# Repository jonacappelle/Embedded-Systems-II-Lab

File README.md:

# LAB: Embedded Systems II

## SOFTWARE

- [IMU](https://github.com/jonacappelle/Embedded-Systems-II-Lab/tree/master/Jona%20-%20IMU%20and%20Main%20PCB/Embedded_II_ICM_20948)
- [Game](https://github.com/jonacappelle/Embedded-Systems-II-Lab/tree/master/Niels%20-%20Code%20spel/SLSTK3400A_blink)
- [LoRa](https://github.com/jonacappelle/Embedded-Systems-II-Lab/tree/master/Pieter%20-%20Connectivity%20and%20Visualisation)

## HARDWARE

[Main board](https://github.com/jonacappelle/Embedded-Systems-II-Lab/tree/master/Jona%20-%20IMU%20and%20Main%20PCB/EFM32_ICM20948_PCB)  
[Energy harvesting](https://github.com/jonacappelle/Embedded-Systems-II-Lab/tree/master/Daan%20-%20VoedingDesign%20PCB/schema_pcb)

### MAIN BOARD: µC + Compass + LoRa

### POWER BOARD

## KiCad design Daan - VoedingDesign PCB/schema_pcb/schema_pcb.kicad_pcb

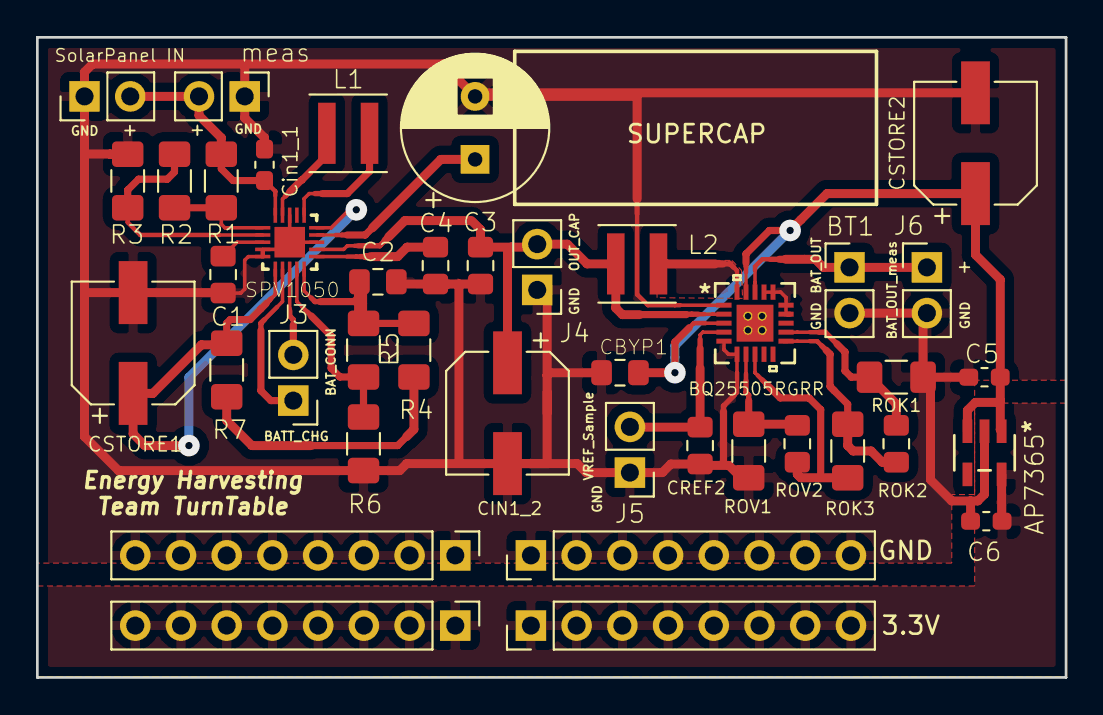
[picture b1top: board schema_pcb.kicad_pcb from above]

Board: 2 copper layers, 57.2 x 35.6 mm, 37 parts (0 on the bottom side), 24 nets.

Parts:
3.3V: Conn_3V3_2; PinHeader_1x08_P2.54mm_Vertical
BT1: Battery_Cell; PinHeader_1x02_P2.54mm_Vertical
C1: 10 nF; C_0805_2012Metric_Pad1.15x1.40mm_HandSolder
C2: 470 nF; C_0805_2012Metric_Pad1.15x1.40mm_HandSolder
C3, C4: 100 nF; C_0805_2012Metric_Pad1.15x1.40mm_HandSolder
C5, C6: 1u; C_0603_1608Metric_Pad1.05x0.95mm_HandSolder
CBYP1: 0.1 uF; C_0805_2012Metric_Pad1.15x1.40mm_HandSolder
CIN1_2: 4.7 uF; CP_Elec_6.3x5.3
CREF2: 100 nF; C_0805_2012Metric_Pad1.15x1.40mm_HandSolder
CSTORE1: 47 uF; CP_Elec_6.3x5.3
CSTORE2: 4.7 uF; CP_Elec_6.3x5.3
Cin1_1: 1 uF; C_0603_1608Metric_Pad1.05x0.95mm_HandSolder
GND: Conn_GND; PinHeader_1x08_P2.54mm_Vertical
J3: output_connect_pins; PinHeader_1x02_P2.54mm_Vertical
J4: conn_supercap_meas_volt; PinHeader_1x02_P2.54mm_Vertical
J5: conn_meas_VREF_Sample; PinHeader_1x02_P2.54mm_Vertical
J6: conn_meas_battery; PinHeader_1x02_P2.54mm_Vertical
L1, L2: 22 uH; L_Coilcraft_XxL4040
R1: 10 M; R_1206_3216Metric_Pad1.42x1.75mm_HandSolder
R2: 560 K; R_1206_3216Metric_Pad1.42x1.75mm_HandSolder
R3: 2.7 M; R_1206_3216Metric_Pad1.42x1.75mm_HandSolder
R4: 3.9 M; R_1206_3216Metric_Pad1.42x1.75mm_HandSolder
R5: 1.5 M; R_1206_3216Metric_Pad1.42x1.75mm_HandSolder
R6: 7.5 M; R_1206_3216Metric_Pad1.42x1.75mm_HandSolder
R7: 3.3 M; R_1206_3216Metric_Pad1.42x1.75mm_HandSolder
ROK1: 5.23; R_1206_3216Metric_Pad1.42x1.75mm_HandSolder
ROK2: 6.34 M; R_0805_2012Metric_Pad1.15x1.40mm_HandSolder
ROK3: 1.3 M; R_1206_3216Metric_Pad1.42x1.75mm_HandSolder
ROV1: 5.62 M; R_1206_3216Metric_Pad1.42x1.75mm_HandSolder
ROV2: 7.32 M; R_0805_2012Metric_Pad1.15x1.40mm_HandSolder
SPV1050: SPV1050TTR; QFN40P300X300X100-21N
SUPERCAP: 3.3 F; CP_Radial_D8.0mm_P3.50mm
SolarPanel IN: conn_solarpanel; PinHeader_1x02_P2.54mm_Vertical
meas: conn_meas_solarpanel; PinHeader_1x02_P2.54mm_Vertical

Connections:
/BatteryLoader/input: C3.1, CIN1_2.1, J4.2, L2.2, SPV1050.12
GND: BT1.2, C1.1, C2.2, C3.2, C4.2, C5.2, C6.2, CBYP1.2, CIN1_2.2, CREF2.2, CSTORE1.2, CSTORE2.2, Cin1_1.2, GND.1, GND.2, GND.3, GND.4, GND.5, GND.6, GND.7, GND.8, J4.1, J5.1, J6.2, R3.2, R6.1, ROK1.2, ROV1.2, SPV1050.4, SPV1050.5, SPV1050.13, SPV1050.18, SPV1050.21, SUPERCAP.2, SolarPanel IN.1, meas.1
unnamed: BT1.1, J6.1
unnamed: C1.2, SPV1050.3
unnamed: C2.1, R4.1, R5.2, SPV1050.10
unnamed: C4.1, SPV1050.11
unnamed: C5.1, CBYP1.1, CSTORE2.1
unnamed: 3.3V.1, 3.3V.2, 3.3V.3, 3.3V.4, 3.3V.5, 3.3V.6, 3.3V.7, 3.3V.8, C6.1
unnamed: CREF2.1, J5.2
unnamed: CSTORE1.1, R7.2, SPV1050.6, SPV1050.15
unnamed: Cin1_1.1, R1.1, SPV1050.20, SolarPanel IN.2, meas.2
unnamed: J3.1, SPV1050.7
unnamed: J3.2, SPV1050.8
unnamed: L1.1, SPV1050.19
unnamed: L1.2, SPV1050.16
unnamed: R1.2, R2.1, SPV1050.1
unnamed: R2.2, R3.1, SPV1050.2
unnamed: R4.2, R7.1
unnamed: R5.1, R6.2, SPV1050.9
unnamed: ROK1.1, ROK2.2
unnamed: ROK2.1, ROK3.2
unnamed: ROK3.1, ROV2.1
unnamed: ROV1.1, ROV2.2
unnamed: SPV1050.14, SUPERCAP.1

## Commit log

2020-03-27 Compass working (not tilt-compensated)
2020-03-27 Hardware main board v0.1
2020-03-27 pcb files + file pinnen
2020-03-27 start tekenen PCB
2020-03-29 schema getekend (bijna af), nog pcb routing
2020-03-30 schema getekend voeding_ bijna alle footprints volledig
2020-03-31 afgewerkte Energy Harvesting PCB
2020-04-01 main board pcb
2020-04-01 Routing main pcb
2020-04-01 main pcb lora update, bijna klaar
2020-04-01 renders voedings pcb
2020-04-02 finalisatie design main pcb (uC + imu + lora)
2020-04-03 PCB's DONE! :100:
2020-04-08 viasAangepast
2020-04-17 INFObestellingenzo
2020-04-17 update PCB + code + graphs
2020-04-17 update pcb + door te sturen info
2020-04-17 aanvulling niels
2020-04-17 schema toegevoegd
2020-04-18 embedded
2020-04-24 LoRa - Team Turn Table - Simplicity Studio Export
    Not the final version
    Sends student/emplyee number and players' score to The Things Network
2020-04-30 Verslag begin + ppt
2020-05-02 batturl
2020-05-02 Pieter - Player + Score (EFM32) -> Website
    EFM32 Lora (Player & Score) -> TTN Payload decoder -> Swagger API -> Mysql database -> Website
2020-05-02 Create Pieter - EFM32 -> Website
2020-05-02 Create 1
2020-05-02 Turntable Highscore Website
    Discription: Displays today's highscores, all time highscores and latest gameplays of Turntable Game Technologiecampus Gent from mysql database.
    Table items:
    *Medal for best 3 players
    *All time rank
    *Student/employee number
    *The player's scores
2020-05-02 The Things Network - Payload Decoder
    Decodes RAW bytes send trough LORA to playerId and playerScore in json format
2020-05-02 Swagger API data to Mysql database
    Python script with 1 minute execute interval to retreive data from temporary TTN database to permanent MYSQL database
2020-05-02 Send player Id and Score via RN2483 Lora on EFM32
    Silicon Labs Export
    *Encode playerId and playerScore to RAW bytes
    *Send bytes via RN2483 lora module
    *EFM32 Happy Gecko development board
2020-05-02 verslagDaan
2020-05-02 test
    test
2020-05-02 Connectivity and Visualisation
2020-05-03 Samenvoeging verslag Jona, Daan, Pieter
2020-05-05 Toevoeging deel Tuur
2020-05-06 adres wijziging
2020-05-06 verbeterd verslag
2020-05-06 code simon
2020-05-06 verslag
2020-05-06 Opmerkingen Tuur verbeterd, besluit nog schrijven!
    Alvast wat punten voor het besluit toegevoegd.
2020-05-07 Aangepaste verantwoordelijkheden
2020-05-07 besluit
2020-05-07 Verslag DONE!
2020-05-07 Opkuis + sorteren
2020-05-11 Eindpresentatie deel Pieter
2020-05-12 Aanpassingen pieter (korter)
2020-05-13 Eindpresentatie :100:

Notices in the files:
parts and their libraries:
Copyright 2016 Accelerated Designs. All rights reserved.
